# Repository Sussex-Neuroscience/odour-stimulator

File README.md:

# Odour stimulator - A fast, time precise open source system to deliver odours. 

## This open source stimulator is based on previous work by a different group. Their work is published  [here](https://www.pnas.org/content/111/47/16925), [here](https://www.sciencedirect.com/science/article/pii/S2589004218300646) and [here](<https://academic.oup.com/chemse/article/42/2/141/2709444>)

The image below is taken from https://academic.oup.com/chemse/article/42/2/141/2709444

--- 
## Some information about this project:

- developed as part of the work of the [Nowotny lab](https://www.sussex.ac.uk/research/centres/sussex-neuroscience/phd/4yearphd/supervisors/circuits-projects/thomas-nowotny-project) and it is being setup initially for experiments with flies. 
- The reason we are publicly documenting things is that since the original papers describing the stimulator came out, some enabling technology has become widely available, which makes setting this up simpler and less expensive. This write up is our attempt to document this.
- Some documentation of the orignal stimulator is already publicly available on [github already](https://github.com/grg2rsr/OlfactoryStimulator), unfortunately some of the schematics are only in PDF format (which prevents fast conversion to PCBs) and some of the CAD files are in a proprietary format, that officially can only be read with "Autodesk Inventor". Luckily there is a [plugin for FreeCad](https://github.com/jmplonka/InventorLoader/) that allows the conversion to a more open format.  This derivative will share orignal files that can be modified using open source sofware.

---

### main differences from the original papers:

- Since it would be quite expensive to reproduce the PEEK machined part they describe on the paper, we bought polypropylene filament and we printing the part. There are a couple of differences in between the two processes, and the derivatitve designs we made are optimised for printing. 
  
- Several online resources show tips and guides on how to print with this material:
 - https://www.lpfrg.com/guides/3d-printing-polypropylene/
 - https://all3dp.com/2/3d-printing-polypropylene-how-to-3d-print-with-pp/
 - https://www.simplify3d.com/support/materials-guide/polypropylene/
 - https://www.youtube.com/watch?v=yRw2mC_6A00 

- The electronics in this project but emphasis on using a microncontroller for timing control and connectivity with other devices. More specifically we are using an ESP32 and micropython to integrate the system with other devices/computers.

### repository structure:

#### repository link: https://github.com/Sussex-Neuroscience/odour-stimulator

#### tags: 
hardware,behaviour,electrophysiology,drosophila

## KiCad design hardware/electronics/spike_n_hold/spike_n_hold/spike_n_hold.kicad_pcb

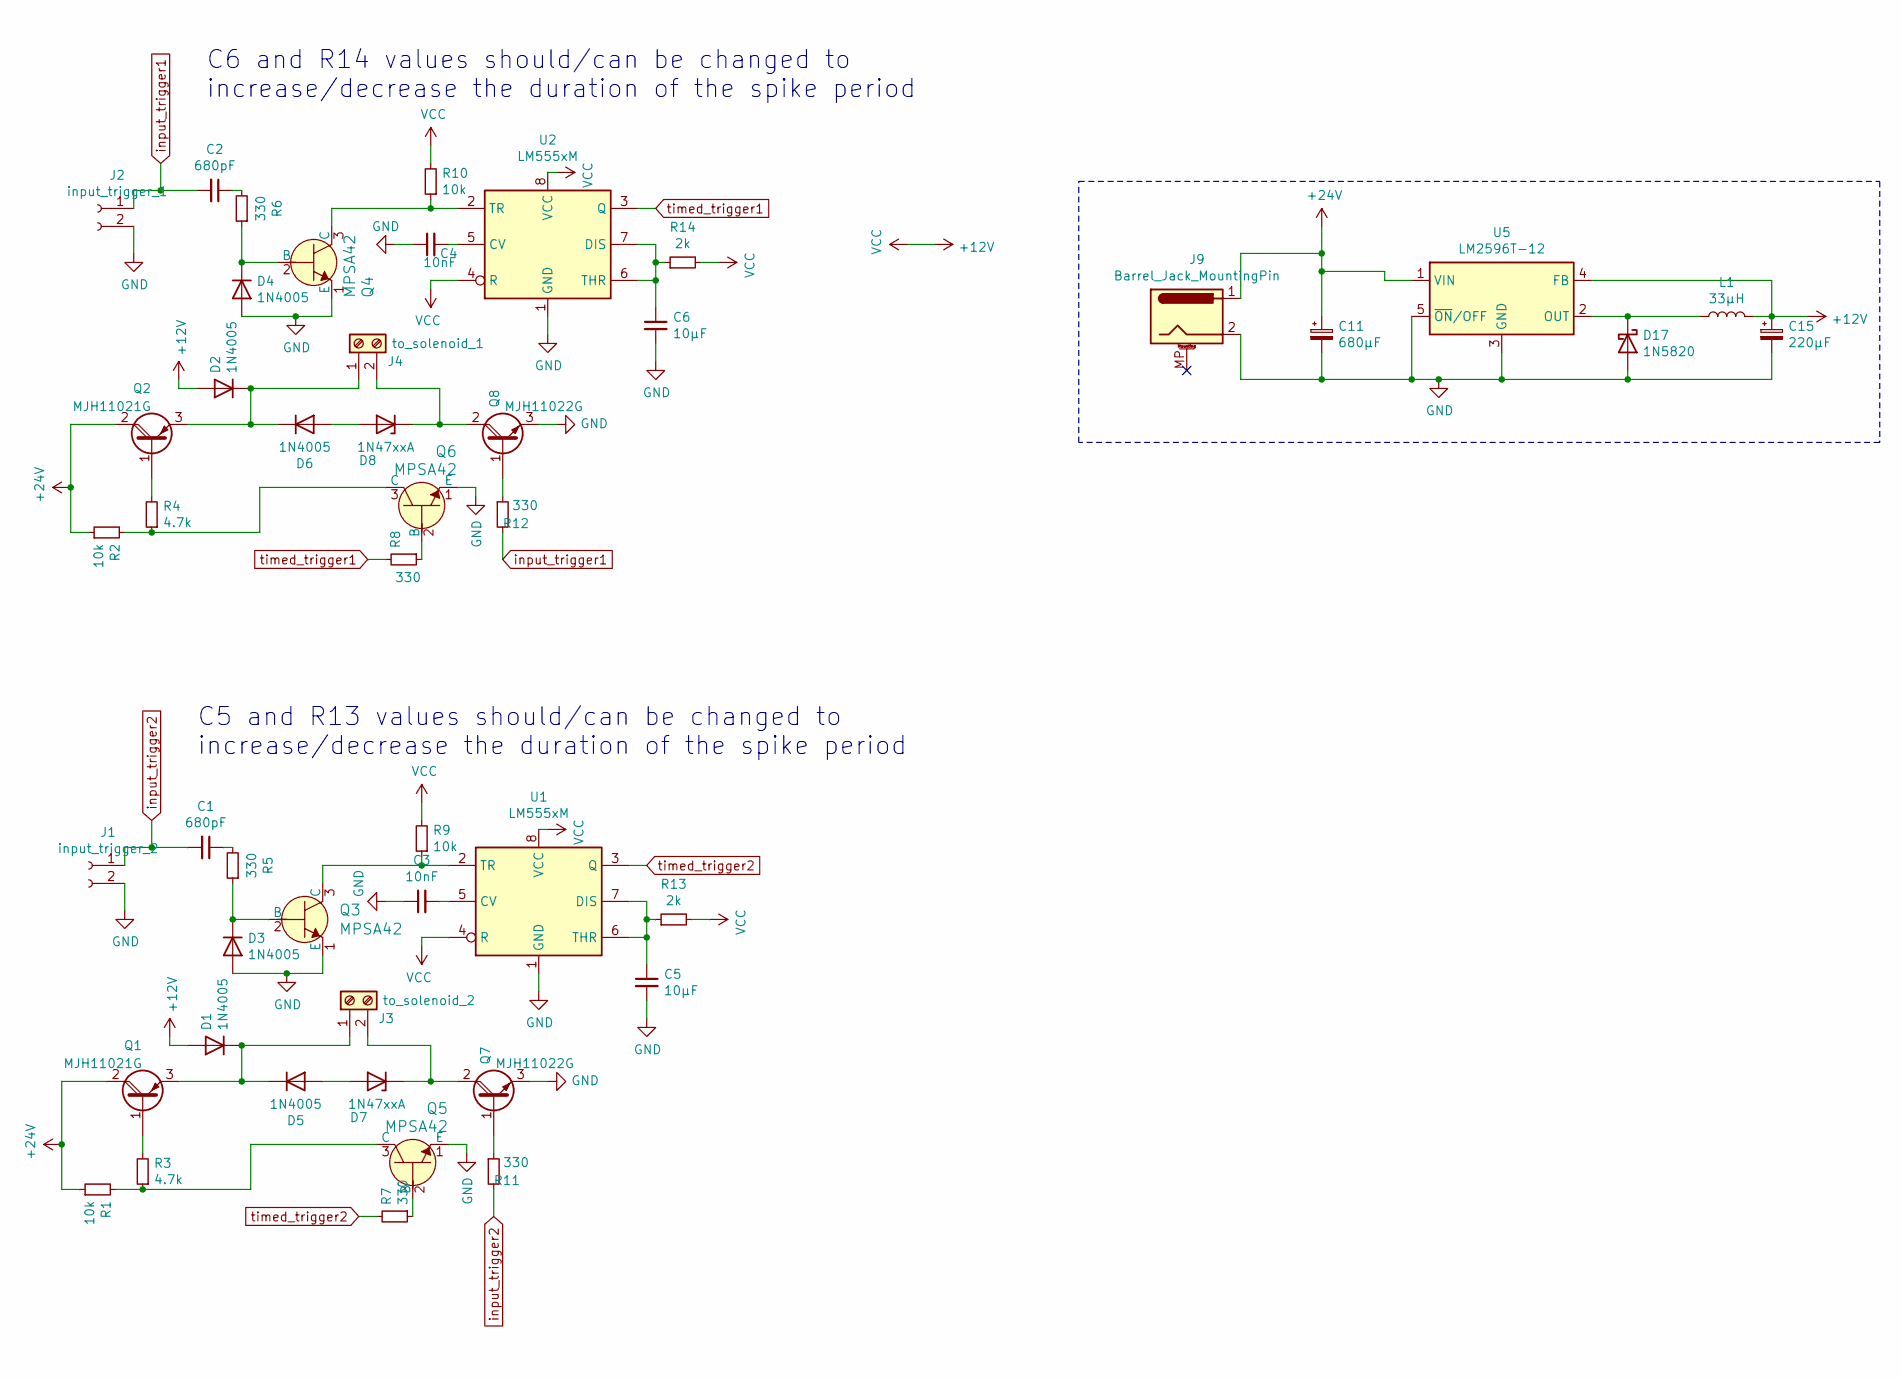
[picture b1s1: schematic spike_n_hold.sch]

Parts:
C1, C2: 680pF; C_Disc_D5.1mm_W3.2mm_P5.00mm
C3, C4: 10nF; C_Disc_D5.1mm_W3.2mm_P5.00mm
C5, C6: 10µF; C_Disc_D5.1mm_W3.2mm_P5.00mm
C11: 680µF; CP_Radial_D10.0mm_P5.00mm
C15: 220µF; CP_Radial_D10.0mm_P5.00mm
D1, D2, D3, D4, D5, D6: 1N4005; D_DO-41_SOD81_P10.16mm_Horizontal
D7, D8: 1N47xxA; D_DO-41_SOD81_P10.16mm_Horizontal
D17: 1N5820; D_DO-201AD_P15.24mm_Horizontal
J1: input_trigger_2; PinHeader_1x02_P2.54mm_Vertical
J2: input_trigger_1; PinHeader_1x02_P2.54mm_Vertical
J3: to_solenoid_2; PinHeader_1x02_P2.54mm_Vertical
J4: to_solenoid_1; PinHeader_1x02_P2.54mm_Vertical
J9: Barrel_Jack_MountingPin; Barrel_Jack_5.5mmODx2.1mmID_PJ-202A
L1: 33µH; L_Radial_D7.5mm_P3.50mm_Fastron_07P
Q1, Q2: MJH11021G; TO-247-3_Vertical
Q3, Q4, Q5, Q6: MPSA42; TO-92L_Inline_Wide; MPN MPSA42; Digi-Key_PN MPSA42FS-ND
Q7, Q8: MJH11022G; TO-247-3_Vertical
R1, R2, R9, R10: 10k; R_Axial_DIN0411_L9.9mm_D3.6mm_P12.70mm_Horizontal
R3, R4: 4.7k; R_Axial_DIN0411_L9.9mm_D3.6mm_P12.70mm_Horizontal
R5, R6, R7, R8, R11, R12: 330; R_Axial_DIN0411_L9.9mm_D3.6mm_P12.70mm_Horizontal
R13, R14: 2k; R_Axial_DIN0411_L9.9mm_D3.6mm_P12.70mm_Horizontal
U1, U2: LM555xM; DIP-8_W7.62mm_LongPads
U5: LM2596T-12; TO-220-5_P3.4x3.7mm_StaggerOdd_Lead3.8mm_Vertical

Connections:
+12V: C15.1, D1.2 (A), D2.2 (A), L1.2, R9.2, R10.2, R13.2, R14.2, U1.4 (R), U1.8 (VCC), U2.4 (R), U2.8 (VCC), U5.4 (FB)
+24V: C11.1, J9.1, Q1.2 (C), Q2.2 (C), R1.1, R2.1, U5.1 (VIN)
GND: C3.1, C4.1, C5.2, C6.2, C11.2, C15.2, D3.2 (A), D4.2 (A), D17.2 (A), J1.2, J2.2, J9.2, Q3.1 (E), Q4.1 (E), Q5.1 (E), Q6.1 (E), Q7.3 (E), Q8.3 (E), U1.1 (GND), U2.1 (GND), U5.3 (GND), U5.5 (~ON~/OFF)
unnamed: C1.1, R5.2
unnamed: C2.1, R6.2
unnamed: C3.2, U1.5 (CV)
unnamed: C4.2, U2.5 (CV)
unnamed: C5.1, R13.1, U1.6 (THR), U1.7 (DIS)
unnamed: C6.1, R14.1, U2.6 (THR), U2.7 (DIS)
unnamed: D1.1 (K), D5.1 (K), J3.1, Q1.3 (E)
unnamed: D2.1 (K), D6.1 (K), J4.1, Q2.3 (E)
unnamed: D3.1 (K), Q3.2 (B), R5.1
unnamed: D4.1 (K), Q4.2 (B), R6.1
unnamed: D5.2 (A), D7.2 (A)
unnamed: D6.2 (A), D8.2 (A)
unnamed: D7.1 (K), J3.2, Q7.2 (C)
unnamed: D8.1 (K), J4.2, Q8.2 (C)
unnamed: D17.1 (K), L1.1, U5.2 (OUT)
unnamed: Q1.1 (B), R3.2
unnamed: Q2.1 (B), R4.2
unnamed: Q3.3 (C), R9.1, U1.2 (TR)
unnamed: Q4.3 (C), R10.1, U2.2 (TR)
unnamed: Q5.2 (B), R7.1
unnamed: Q5.3 (C), R1.2, R3.1
unnamed: Q6.2 (B), R8.1
unnamed: Q6.3 (C), R2.2, R4.1
unnamed: Q7.1 (B), R11.1
unnamed: Q8.1 (B), R12.1
input_trigger1: C2.2, J2.1, R12.2
input_trigger2: C1.2, J1.1, R11.2
timed_trigger1: R8.2, U2.3 (Q)
timed_trigger2: R7.2, U1.3 (Q)

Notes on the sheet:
C6 and R14 values should/can be changed to increase/decrease the duration of the spike period
C5 and R13 values should/can be changed to increase/decrease the duration of the spike period

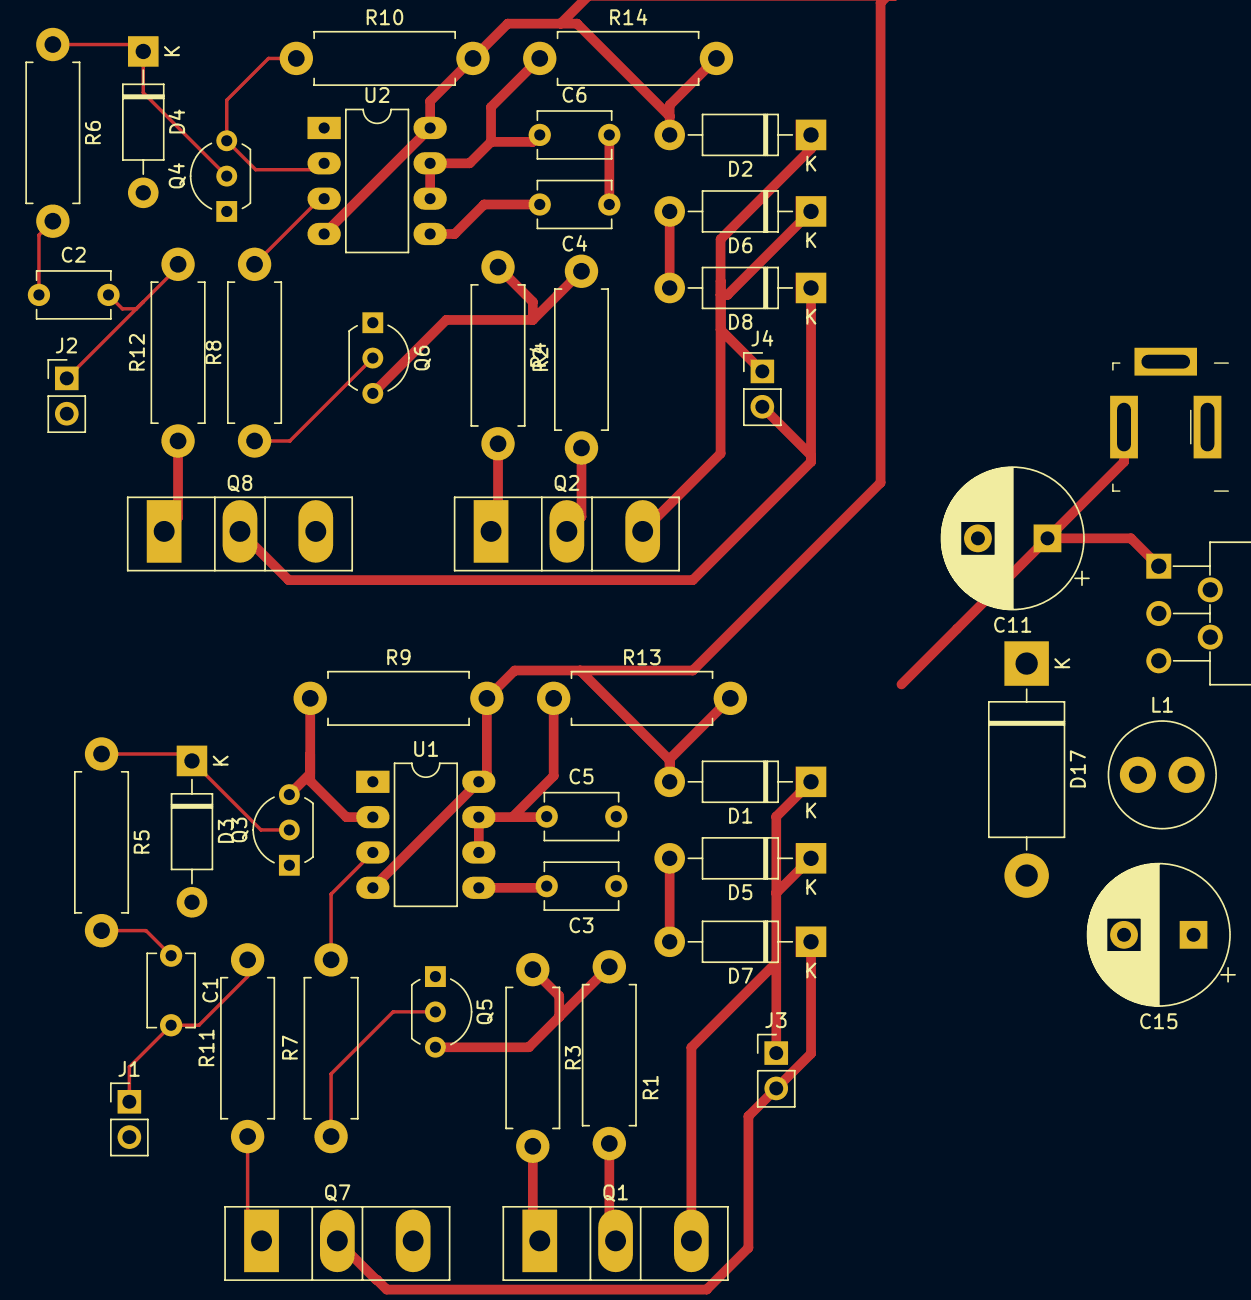
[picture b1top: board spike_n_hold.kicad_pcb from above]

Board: 2 copper layers, 48 parts (0 on the bottom side), 32 nets.

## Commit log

2020-01-14 add github repo from previous paper to "related projects"
2020-01-14 remove dev plan file
2020-02-11 initial clean up and uploading files
2020-02-11 more documentation work
2020-02-11 clean up bill of materials. Splitting it into electronics and mechanics for now
2020-02-12 more updates to BOMs
2020-02-12 syntax correction
2020-02-12 correct link
2020-02-12 corrections to bom, plus some more additions
2020-02-12 correction to gauge in BOM
2020-02-12 converted all autodesk inventor to files readable in freecad
2020-02-17 created bill of materials for mechanical parts as well as gcode and amf files for central body
2020-02-17 added more parts to BOM
2020-02-17 correct bom entries
2020-02-18 update mechanical bom
2020-02-27 prepare gcode for printing with PP
2020-03-06 gcode for printing
2020-06-11 workstation
2020-08-04 update to 3D printed parts and readme
2020-08-10 revamp mechanical parts for printing and update readme
2020-10-29 initial design for rotameter holder
2020-10-29 add stl file
2020-10-29 both models
2020-10-30 add individual STLs and tweak design
2020-11-04 add gitignore so to remove upload of unnecessary files
2020-11-04 rewrite readme
2020-11-04 update readme image
2021-01-13 schematics of the spike and hold circuitry
2021-01-13 update mechanics
2021-01-13 fix capacitor value
2021-01-28 last implementation of the 6 spike and trigger board.
2021-01-28 reimplementation, 2 modules per board, as they are equivalent to one odour channel, or one dilution step
2021-03-01 central body measurements and luer fitting print test
2021-03-10 fix bug on board, upload some documents, clean up repo (delete unused folders) and upload some iterations of the printed body
2021-03-10 prepare for kitspace
2021-03-10 add figure reference in readme
2021-04-19 fix orientation of valves and diameter of opening
2021-04-20 main block updates: side channels inside block now leave at an angle to facilitate 3D printing and valves are positioned at 45 degrees. This enables valves to be placed 'upside down' so that exhaust 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
2021-04-26 start building documentation
2021-04-27 make fittings for rotameters and tubes
2021-04-27 resolve flowmeter to tube adapter
2021-04-28 final cleanup on printed parts for attaching tubes to flowmeters
2021-04-28 rearrange folder structure
2021-05-05 remove excessive track on board (two ground tracks going to same place), add + sign on polar capacitors, add 3D models for connectors
2021-05-18 updated mechanics
2021-05-18 upload stl
2021-08-20 updated version of central block
2021-10-06 small changes to readme so the readme2post tool can be tested
2021-11-03 adapt main body for thinner input tubes
2021-12-07 update main block
2023-08-04 add media
